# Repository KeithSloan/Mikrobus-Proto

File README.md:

# Mikrobus-Prototype PCB
### New Design 
Having looked at using the protype board I have made some changes to hopefully make it more flexible. The new board is the **Mikrobus-Proto-22**. 
I have kept the old design files for completeness.
### Mikrobus
I have a [pi2-shield](http://www.mikroe.com/click/pi2-shield/) for my Raspberry Pi B+
and decide to develop an alternative prototype board for the MikronElectronika Mikrobus [http://www.mikroe.com/click/proto/]
as I am not keen on creating solder bridges or wirewraping.
Mikrobus devices are of course usable with Raspberry Pi, Beagle Bone Black and Arduino
### PCB Software
Designed with Cadsofts Free version of Eagle [http://www.cadsoftusa.com/download-eagle/freeware/]
### File Availabity
Files are available at Github [https://github.com/KeithSloan/Mikrobus-Proto]

To obtain the Eagle files run the following command
**git clone https://github.com/KeithSloan/Mikrobus-Proto.git**
### Main Eagle Files
1. Schematic: Mikrobus-Proto-22.sch
2. PCB:       Mikrobus-Proto-22.brd
3. Project:   Mikrobus-Proto-22.pro

### Old Design
4. Schematic: Mikrobus-Proto-18.sch
5. PCB:       Mikrobus-Proto-18.brd
6. Project:   Mikrobus-Proto-18.pro

#### Library of componenets used
4. Library:  KS Proto.lbr

### The following Gerber Files were created in RS-274x format with a Excellon format drill file
1. Mikrobus-Proto-22.cmp (Copper, component side)
2. Mikrobus-Proto-22.drd (Drill file)
3. Mikrobus-Proto-22.dri (Drill Station Info File) 
4. Mikrobus-Proto-22.gpi (Photoplotter Info File)
5. Mikrobus-Proto-22.plc (Silk screen, component side)
6. Mikrobus-Proto-22.pls (Silk screen, solder side)
7. Mikrobus-Proto-22.sol (Copper, solder side)
8. Mikrobus-Proto-22.stc (Solder stop mask, component side)
9. Mikrobus-Proto-22.sts (Solder stop mask, solder side)

10. Mikrobus-Proto-18.zip (The above Gerber files zipped together for sending to Fab)
11. zipGerber.sh ( Shell script to produce zip file )

For board fabrication I use [https://www.itead.cc/open-pcb/pcb-prototyping.html]

### Feedback
Constructive feedback to keith@sloan-home.co.uk

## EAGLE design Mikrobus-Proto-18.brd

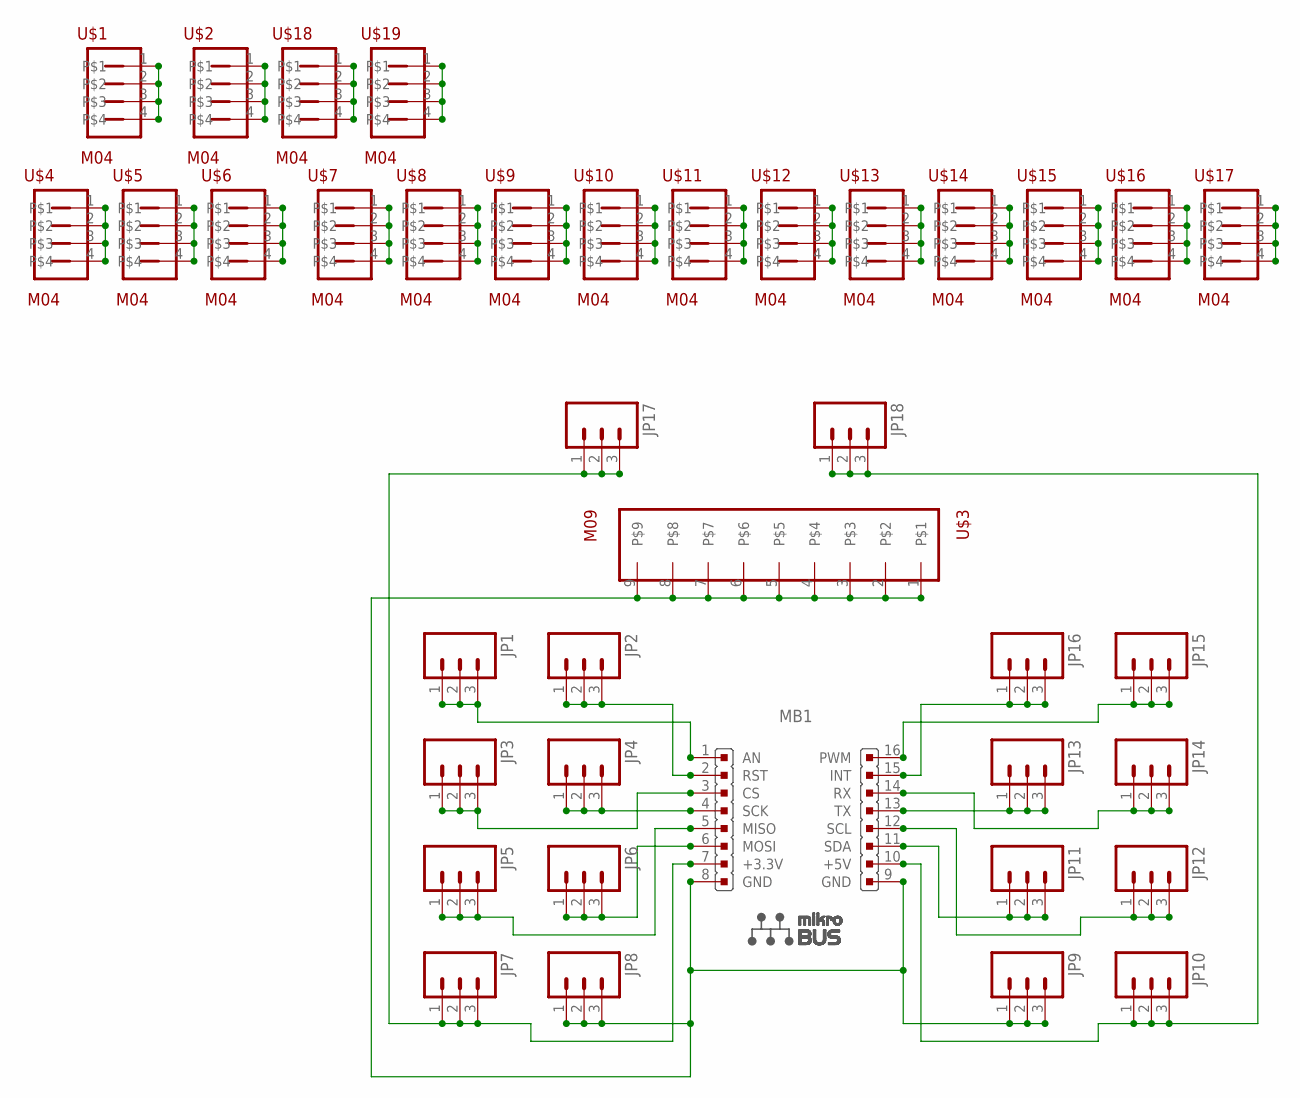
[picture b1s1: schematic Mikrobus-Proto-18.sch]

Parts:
JP1, JP2, JP3, JP4, JP5, JP6, JP7, JP8, JP9, JP10, JP11, JP12, JP13, JP14, JP15, JP16, JP17, JP18: M03PTH; 1X03
MB1: MIKROBUS
U$1, U$2, U$4, U$5, U$6, U$7, U$8, U$9, U$10, U$11, U$12, U$13, U$14, U$15, U$16, U$17, U$18, U$19: M04; 1X04
U$3: M09; 1X09

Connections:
+3.3V: JP7.1, JP7.2, JP7.3, JP17.1, JP17.2, JP17.3, MB1.7 (+3.3V)
+5V: JP10.1, JP10.2, JP10.3, JP18.1, JP18.2, JP18.3, MB1.10 (+5V)
AN: JP1.1, JP1.2, JP1.3, MB1.1 (AN)
CS: JP3.1, JP3.2, JP3.3, MB1.3 (CS)
GND: JP8.1, JP8.2, JP8.3, JP9.1, JP9.2, JP9.3, MB1.8 (GND), MB1.9 (GND), U$3.1, U$3.2, U$3.3, U$3.4, U$3.5, U$3.6, U$3.7, U$3.8, U$3.9
INT: JP16.1, JP16.2, JP16.3, MB1.15 (INT)
L1: U$18.1, U$18.2, U$18.3, U$18.4
L2: U$1.1, U$1.2, U$1.3, U$1.4
L3: U$16.1, U$16.2, U$16.3, U$16.4
L4: U$14.1, U$14.2, U$14.3, U$14.4
L5: U$12.1, U$12.2, U$12.3, U$12.4
L6: U$10.1, U$10.2, U$10.3, U$10.4
L7: U$8.1, U$8.2, U$8.3, U$8.4
L8: U$6.1, U$6.2, U$6.3, U$6.4
L9: U$4.1, U$4.2, U$4.3, U$4.4
MISO: JP5.1, JP5.2, JP5.3, MB1.5 (MISO)
MOSI: JP6.1, JP6.2, JP6.3, MB1.6 (MOSI)
PWM: JP15.1, JP15.2, JP15.3, MB1.16 (PWM)
R1: U$19.1, U$19.2, U$19.3, U$19.4
R2: U$2.1, U$2.2, U$2.3, U$2.4
R3: U$17.1, U$17.2, U$17.3, U$17.4
R4: U$15.1, U$15.2, U$15.3, U$15.4
R5: U$13.1, U$13.2, U$13.3, U$13.4
R6: U$11.1, U$11.2, U$11.3, U$11.4
R7: U$9.1, U$9.2, U$9.3, U$9.4
R8: U$7.1, U$7.2, U$7.3, U$7.4
R9: U$5.1, U$5.2, U$5.3, U$5.4
RST: JP2.1, JP2.2, JP2.3, MB1.2 (RST)
RX: JP14.1, JP14.2, JP14.3, MB1.14 (RX)
SCK: JP4.1, JP4.2, JP4.3, MB1.4 (SCK)
SCL: JP12.1, JP12.2, JP12.3, MB1.12 (SCL)
SDA: JP11.1, JP11.2, JP11.3, MB1.11 (SDA)
TX: JP13.1, JP13.2, JP13.3, MB1.13 (TX)

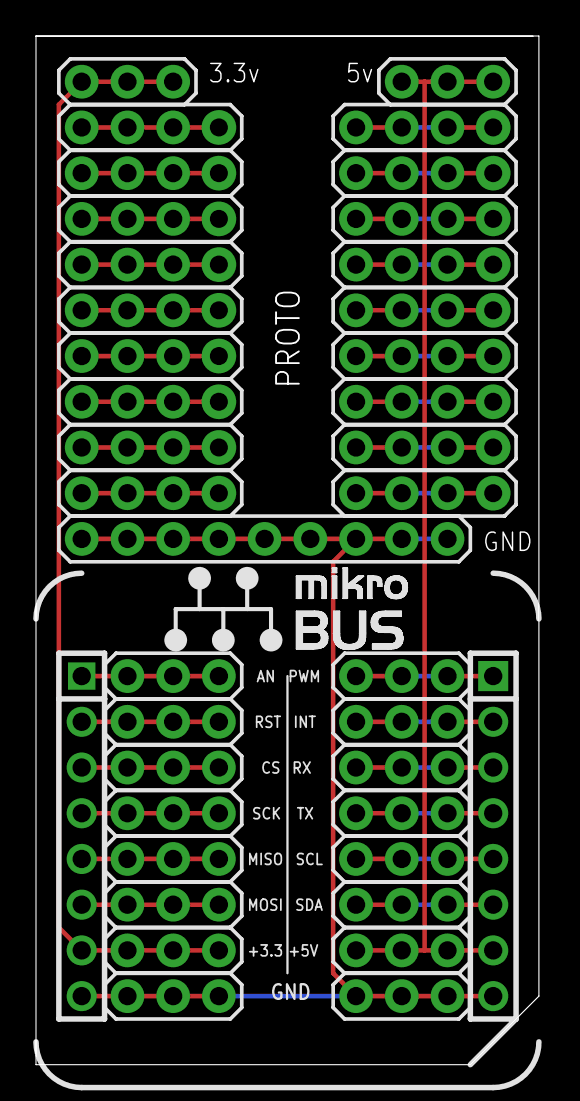
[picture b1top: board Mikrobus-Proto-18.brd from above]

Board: 2 copper layers, 28.2 x 57.1 mm, 38 parts (0 on the bottom side), 33 nets.

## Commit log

2015-12-12 Correct Eagle Library
2015-12-15 Add Ground Plane
2015-12-17 New Design - Mikrobus-Proto-22 added
2015-12-23 Signal names changed for preperation of Fritzing parts
2015-12-25 Addd Fritzing Part
2015-12-25 Rename Fritzing Part to remove spaces
2016-01-16 Added svg files for help in fritzing forum
2016-01-22 Better Fritzing part thanks to Steve Lilley
2016-01-24 Latest Fritzing part from Steve Lilley
2016-01-25 Update to Fritzing part after Steve Lilley discovered Hybrid connectors
2016-01-30 Add Fritzing part for Mikrobus-18 proto board
2016-02-04 Update Proto 18 to latest version
